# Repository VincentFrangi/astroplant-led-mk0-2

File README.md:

# Astroplant Led MK0.2

## About This Project

# AstroPlant LED pannel

Vincent Frangi

## Renderings

### Top

### Bottom

## BOM

|Count|Component|Details|Datasheet|
|-|-|-|-|
|4x||JUMPER W/TEST PNT 1X2PINS 2.54MM||
|4x||CONN HEADER 2 POS 2.54|[Link](http://katalog.we-online.de/em/datasheet/6130xx11121.pdf)|
|6x||CONN HEADER 1 POS 2.54||
|3x||TRIMMER 5K OHM 0.25W SMD||
|3x|R9 / R8 / R7|RES 0 OHM JUMPER 3/4W 2010||
|3x|R6 / R4 / R2|RES SMD 43K OHM 0.1% 1/8W 0805||
|3x|R5 / R3 / R1|RES SMD 3.3K OHM 0.1% 1/8W 0805||
|3x|L3 / L2 / L1|FIXED IND 47UH 2.7A 100 MOHM SMD||
|1x|J2|CONN HEADER XH SMD 3POS 2.5MM||
|1x|J1|CONN HEADER XH SMD 4POS 2.5MM||
|8x|D9 / D8 / D7 / D6 / D5 / D4 / D3 / D2|LED OSLON SSL120 RED 657NM SMD||
|4x|D19 / D18 / D17 / D16|LED OSLON SSL120 RED 727NM SMD||
|4x|D15 / D14 / D13 / D12|LED OSLON SSL120 BLUE 455NM SMD||
|3x|D11 / D10 / D1|DIODE SCHOTTKY 2A 100V SMA||
|3x|C6 / C5 / C2|CAP CER 2.7UF 25V X5R 1206||
|3x|C4 / C3 / C1|CAP CER 1UF 25V X7R 0805|[Link](https://product.tdk.com/info/en/catalog/datasheets/mlcc_commercial_general_en.pdf)|
|3x|U3 / U2 / U1|IC LED DRIVER RGLTR DIM 1A 8SO||

---

This project is managed and available on

You can view it [here](https://aisler.net/p/KXONDWSE). Start your own Powerful Prototype on [here](https://aisler.net).

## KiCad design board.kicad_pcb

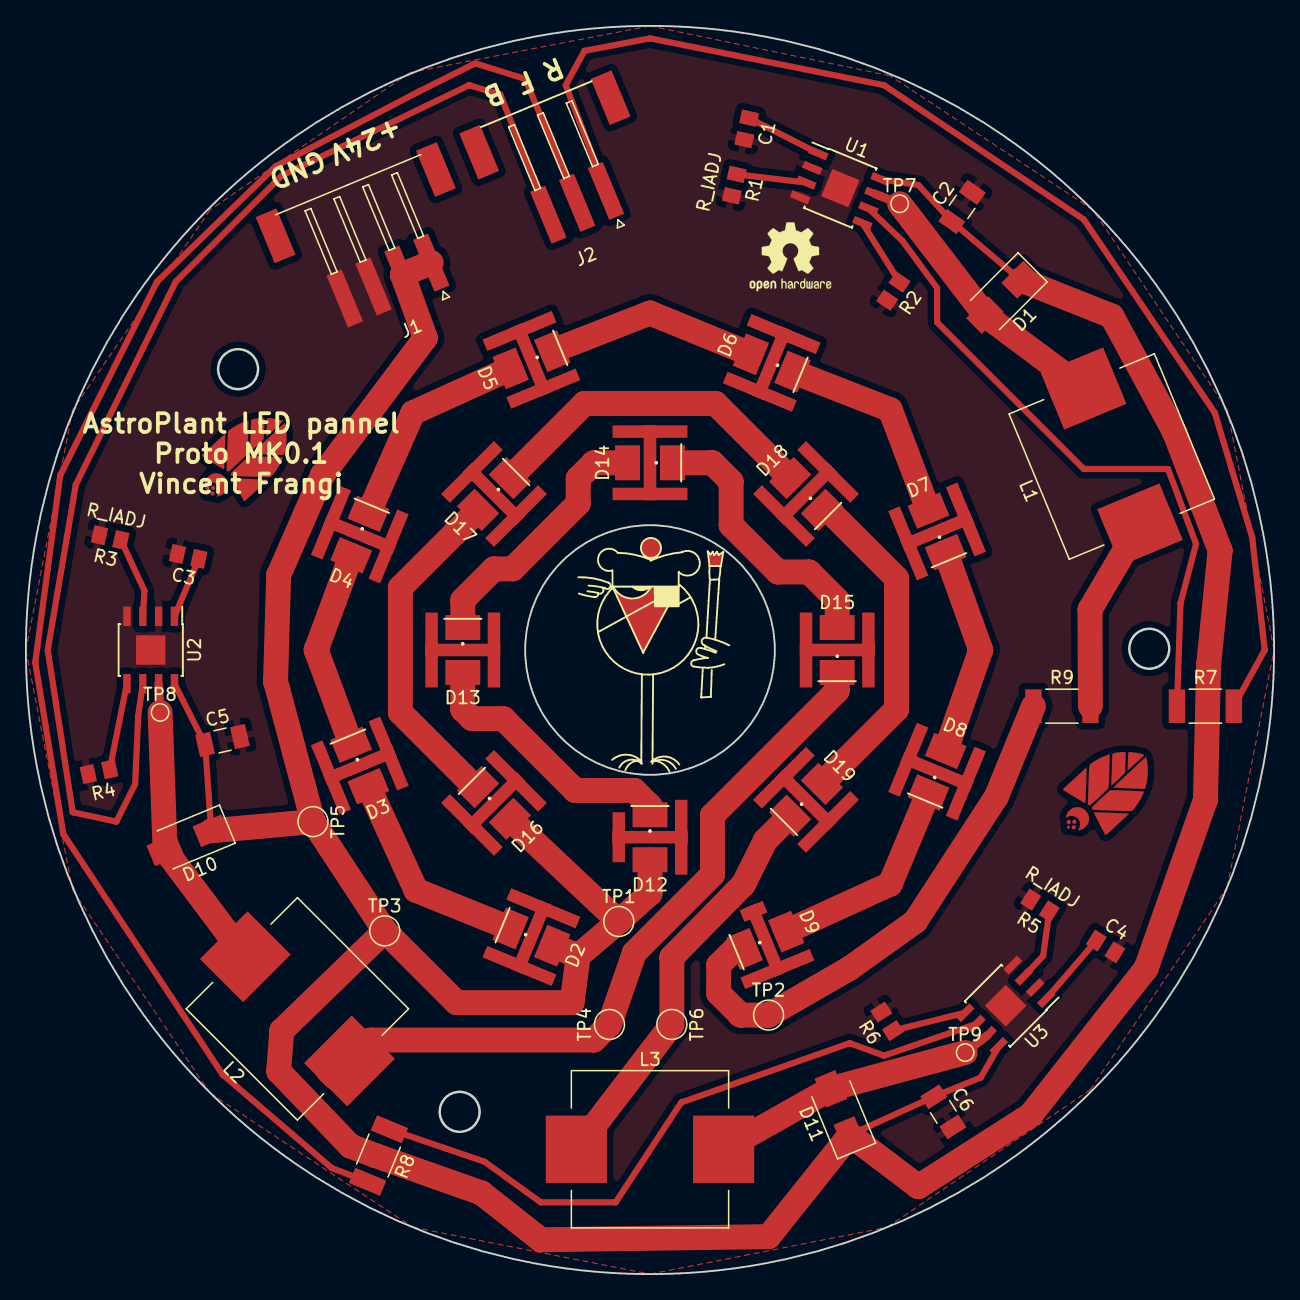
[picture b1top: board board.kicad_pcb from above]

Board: 2 copper layers, 99.9 x 99.9 mm, 51 parts (0 on the bottom side), 36 nets.

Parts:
C1, C3, C4: 1u; C_0805_2012Metric
C2, C5, C6: 2.7u; C_1206_3216Metric
D1, D10, D11: D_Schottky; D_SMA
D2, D3, D4, D5, D6, D7, D8, D9: LED_Red; SSL120
D12, D13, D14, D15: LED_Blue; SSL120
D16, D17, D18, D19: LED_Far; SSL120
J1: JST_XH_LED_POWER
J2: JST-XH_LED
L1, L2, L3: 47u; L_Wuerth_WE-PD-Typ-LS_Handsoldering
R1, R3, R5: 3.3k; R_0805_2012Metric
R2, R4, R6: 43k; R_0805_2012Metric
R7, R8, R9: 0; R_2010_5025Metric
TP1, TP2, TP3, TP4, TP5, TP6: Test_Point; TestPoint_Pad_D2.0mm
TP7, TP8, TP9: Test_Point; TestPoint_Pad_D1.0mm
U1, U2, U3: LM3414; SOIC-8-1EP_3.9x4.9mm_P1.27mm_EP2.35x2.35mm

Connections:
+24V: C2.1, C5.1, C6.1, D1.1, D2.2, D10.1, D11.1, D12.2, D16.2, J1.1, J1.2, TP1.1, TP3.1, TP5.1, U1.8, U2.8, U3.8
DIM_BLUE: J2.3, U2.6
DIM_FAR: R8.1, U3.6
DIM_RED: R7.1, U1.6
GND: C1.2, C2.2, C3.2, C4.2, C5.2, C6.2, J1.3, J1.4, R1.2, R2.2, R3.2, R4.2, R5.2, R6.2, U1.2, U1.4, U1.9, U2.2, U2.4, U2.9, U3.2, U3.4, U3.9
unnamed: C1.1, U1.1
unnamed: C3.1, U2.1
unnamed: C4.1, U3.1
unnamed: D1.2, L1.2, TP7.1, U1.7
unnamed: D2.1, D3.2
unnamed: D3.1, D4.2
unnamed: D4.1, D5.2
unnamed: D5.1, D6.2
unnamed: D6.1, D7.2
unnamed: D7.1, D8.2
unnamed: D8.1, D9.2
unnamed: D9.1, R9.1, TP2.1
unnamed: D10.2, L2.2, TP8.1, U2.7
unnamed: D11.2, L3.2, TP9.1, U3.7
unnamed: D12.1, D13.2
unnamed: D13.1, D14.2
unnamed: D14.1, D15.2
unnamed: D15.1, L2.1, TP4.1
unnamed: D16.1, D17.2
unnamed: D17.1, D18.2
unnamed: D18.1, D19.2
unnamed: D19.1, L3.1, TP6.1
unnamed: J2.1, R7.2
unnamed: J2.2, R8.2
unnamed: L1.1, R9.2
unnamed: R1.1, U1.3
unnamed: R2.1, U1.5
unnamed: R3.1, U2.3
unnamed: R4.1, U2.5
unnamed: R5.1, U3.3
unnamed: R6.1, U3.5

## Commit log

2018-09-21 Syncing AISLER project with GitHub repository
